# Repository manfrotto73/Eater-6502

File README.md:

# Eater-6502
This is a KiCad project that follows Ben Eater's 6502 video series (https://eater.net/6502). I designed the PCB from Ben's schematic.

DISCLAIMER: I am not an EE or a professional PCB designer. I am just a hobbyist who enjoys tinkering w/ electronics and computers. I have no formal training in electrical engineering. Any constructive and educational input is much appreciated.

I have addedd test points on the address and data bus for attaching the Arduino monitor.
The clock has a jumper for access to the internal 1MHz crystal or you can remove the jumper and use Ben's breadboard clock. I also have a pcb for the clock if needed (https://github.com/manfrotto73/Eater-Clock).
There is access to the 8 port "B" lines of the 6522 to attach LED's or a oscilloscope to decode the LCD data if needed. There is a footprint for a current limiting resistor pack (220R) so the LED's will not draw too much current.
I intend to socket all IC's and LED's for ease of troubleshooting or ROM update. Also the LED's are only for the first couple of programs.
Enjoy!
11/29/2019 Schematic and PCB updated to pull the BE pin high to +5V

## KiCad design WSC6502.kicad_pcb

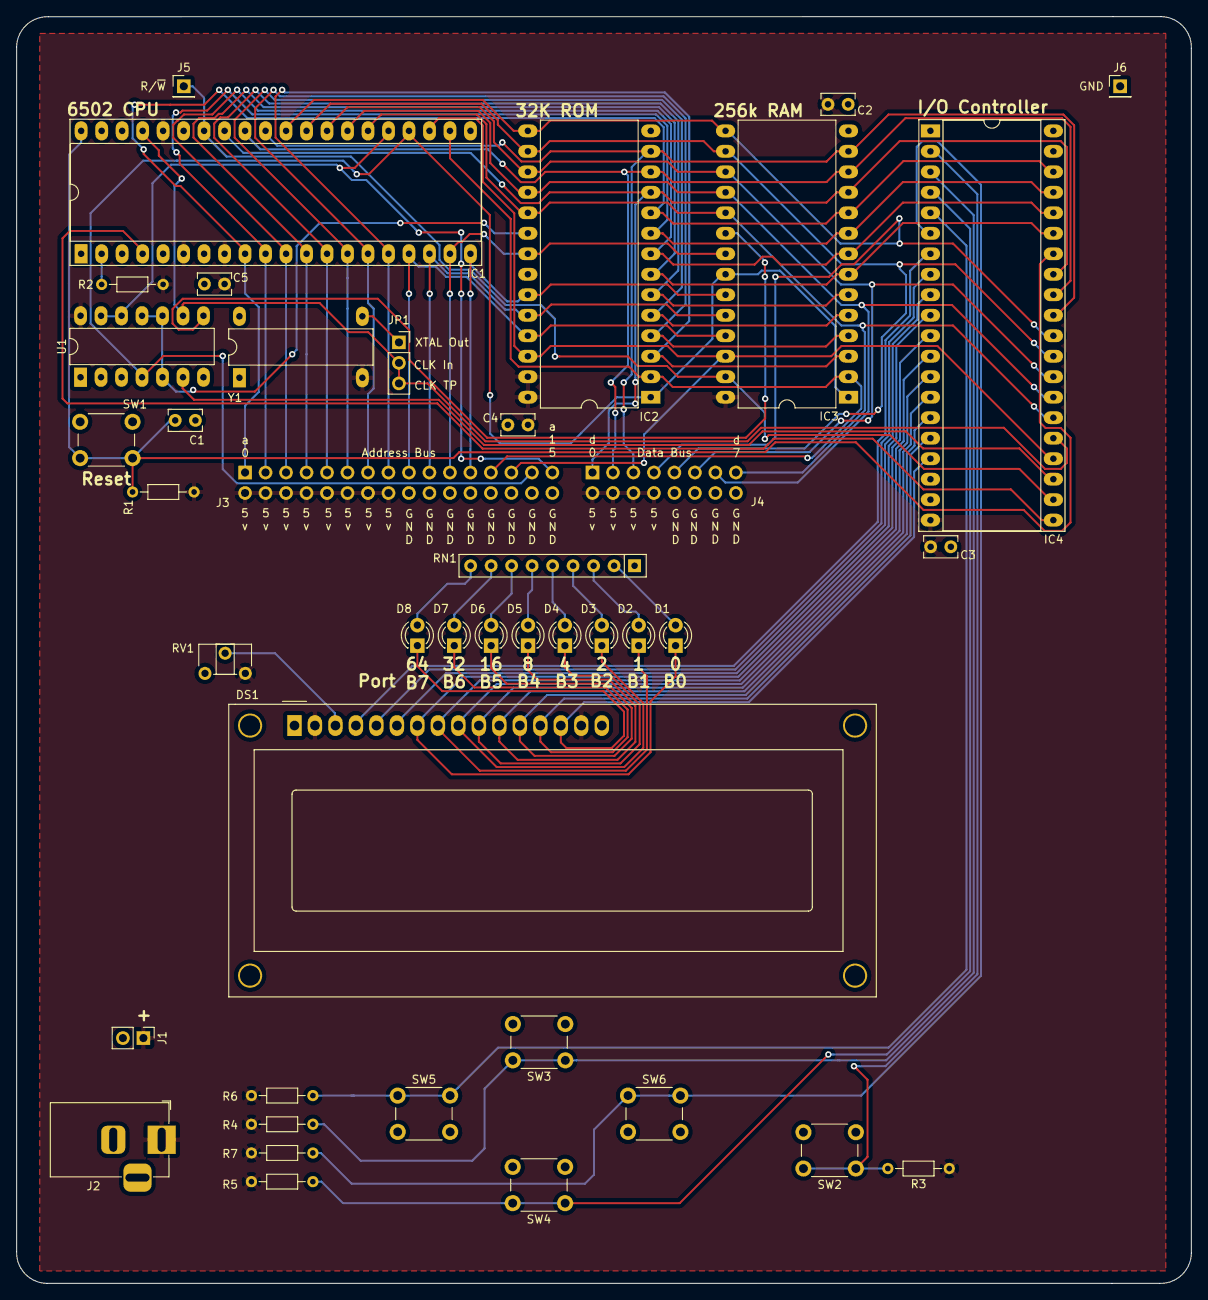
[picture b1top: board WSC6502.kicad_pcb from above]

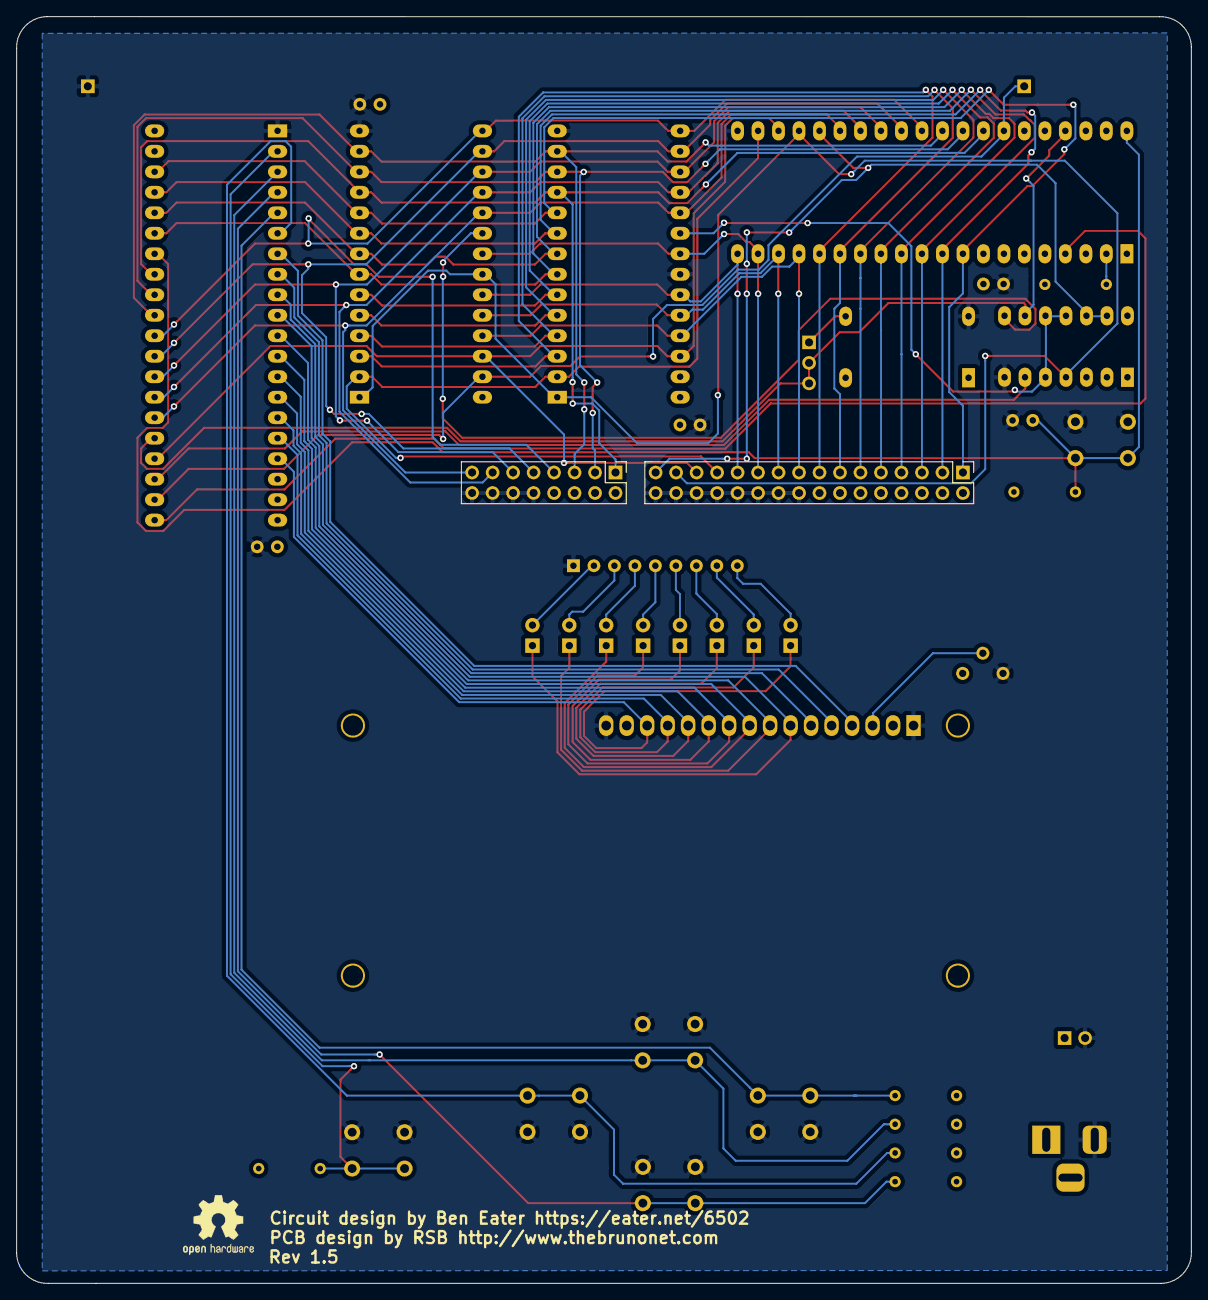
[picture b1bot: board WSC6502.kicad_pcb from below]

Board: 2 copper layers, 145.6 x 157.0 mm, 42 parts (2 on the bottom side), 60 nets.

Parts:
C1, C2, C3, C4, C5: 0.1uF; C_Rect_L4.0mm_W2.5mm_P2.50mm
D1, D2, D3, D4, D5, D6, D7, D8: LED_D3.0mm
DS1: HY1602E; WC1602A
IC1: W65C02S6TPG-14 CPU; DIP-40_W15.24mm_Socket_LongPads
IC2: AT28C256-15PU ROM; DIP-28_W15.24mm_LongPads
IC3: AS6C62256-55PCN SRAM; DIP-28_W15.24mm_LongPads
IC4: W65C22S6TPG-14 I/O; DIP-40_W15.24mm_Socket_LongPads
J1: +5V; PinHeader_1x02_P2.54mm_Vertical
J2: +5V; BarrelJack_Horizontal
J3: Address Bus; PinHeader_2x16_P2.54mm_Vertical
J4: Data Bus; PinHeader_2x08_P2.54mm_Vertical
J5: R~W~ TP; PinHeader_1x01_P2.54mm_Vertical
J6: PinHeader_1x01_P2.54mm_Vertical
JP1: Clock INT / EXT; PinSocket_1x03_P2.54mm_Vertical
R1, R2, R3, R4, R5, R6, R7: 1k; R_Axial_DIN0204_L3.6mm_D1.6mm_P7.62mm_Horizontal
RN1: 220R; R_Array_SIP9
RV1: 10K; Potentiometer_ACP_CA6-H2,5_Horizontal
SW1: Reset; SW_PUSH_6mm_H5mm
SW2, SW3, SW4, SW5, SW6: SW_PUSH_6mm_H5mm
U1: 74HC00; DIP-14_W7.62mm_LongPads
Y1: 1MHz; DIP-14_W7.62mm_LongPads

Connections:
+5V: C2.1, C3.1, C4.1, C5.1, DS1.2, DS1.15, IC1.6, IC1.8, IC1.36, IC2.27, IC2.28, IC3.28, IC4.20, J1.1, J2.1, J3.25, J3.26, J3.27, J3.28, J3.29, J3.30, J3.31, J3.32, J4.13, J4.14, J4.15, J4.16, R1.2, R2.2, R3.1, R4.1, R5.1, R6.1, R7.1, RV1.3, U1.14, Y1.7
/CLK: IC1.37, IC4.25, JP1.2, JP1.3, U1.9
/DS1-Ena: DS1.6, IC4.9
/DS1-RS: DS1.4, IC4.7
/DS1-R~W: DS1.5, IC4.8
/DS1-V0: DS1.3, RV1.2
/R~W: IC1.34, IC3.27, IC4.22, J5.1
/a0: IC1.9, IC2.10, IC3.10, IC4.38, J3.1
/a1: IC1.10, IC2.9, IC3.9, IC4.37, J3.2
/a2: IC1.11, IC2.8, IC3.8, IC4.36, J3.3
/a3: IC1.12, IC2.7, IC3.7, IC4.35, J3.4
/a4: IC1.13, IC2.6, IC3.6, J3.5
/a5: IC1.14, IC2.5, IC3.5, J3.6
/a6: IC1.15, IC2.4, IC3.4, J3.7
/a7: IC1.16, IC2.3, IC3.3, J3.8
/a8: IC1.17, IC2.25, IC3.25, J3.9
/a9: IC1.18, IC2.24, IC3.24, J3.10
/a10: IC1.19, IC2.21, IC3.21, J3.11
/a11: IC1.20, IC2.23, IC3.23, J3.12
/a12: IC1.22, IC2.2, IC3.2, J3.13
/a13: IC1.23, IC2.26, IC3.26, IC4.24, J3.14
/a14: IC1.24, IC2.1, IC3.1, IC3.22, J3.15, U1.4
/a15: IC1.25, J3.16, U1.12, U1.13
/d0: IC1.33, IC2.11, IC3.11, IC4.33, J4.1
/d1: IC1.32, IC2.12, IC3.12, IC4.32, J4.2
/d2: IC1.31, IC2.13, IC3.13, IC4.31, J4.3
/d3: IC1.30, IC2.15, IC3.15, IC4.30, J4.4
/d4: IC1.29, IC2.16, IC3.16, IC4.29, J4.5
/d5: IC1.28, IC2.17, IC3.17, IC4.28, J4.6
/d6: IC1.27, IC2.18, IC3.18, IC4.27, J4.7
/d7: IC1.26, IC2.19, IC3.19, IC4.26, J4.8
/~CE~: IC3.20, U1.8
/~CS2~: IC4.23, U1.6
/~IRQ~: IC1.4, IC4.21
/~Reset: C1.1, IC1.40, IC4.34, R1.1, SW1.2
GND: C1.2, C2.2, C3.2, C4.2, C5.2, DS1.1, DS1.16, IC1.21, IC2.14, IC2.22, IC3.14, IC4.1, J1.2, J2.2, J3.17, J3.18, J3.19, J3.20, J3.21, J3.22, J3.23, J3.24, J4.9, J4.10, J4.11, J4.12, J6.1, RN1.1, RV1.1, SW1.1, SW2.2, SW3.2, SW4.2, SW5.2, SW6.2, U1.7, Y1.14
unnamed: D1.2, RN1.2
unnamed: D2.2, RN1.3
unnamed: D3.2, RN1.4
unnamed: D4.2, RN1.5
unnamed: D5.2, RN1.6
unnamed: D6.2, RN1.7
unnamed: D7.2, RN1.8
unnamed: D8.2, RN1.9
unnamed: IC1.2, R2.1
unnamed: IC2.20, U1.5, U1.10, U1.11
unnamed: IC4.2, R3.2, SW2.1
unnamed: IC4.3, R4.2, SW3.1
unnamed: IC4.4, R5.2, SW4.1
unnamed: IC4.5, R6.2, SW5.1
unnamed: IC4.6, R7.2, SW6.1
unnamed: JP1.1, Y1.8
PB0-DS1-D0: D1.1, DS1.7, IC4.10
PB1-DS1-D1: D2.1, DS1.8, IC4.11
PB2-DS1-D2: D3.1, DS1.9, IC4.12
PB3-DS1-D3: D4.1, DS1.10, IC4.13
PB4-DS1-D4: D5.1, DS1.11, IC4.14
PB5-DS1-D5: D6.1, DS1.12, IC4.15
PB6-DS1-D6: D7.1, DS1.13, IC4.16
PB7-DS1-D7: D8.1, DS1.14, IC4.17
